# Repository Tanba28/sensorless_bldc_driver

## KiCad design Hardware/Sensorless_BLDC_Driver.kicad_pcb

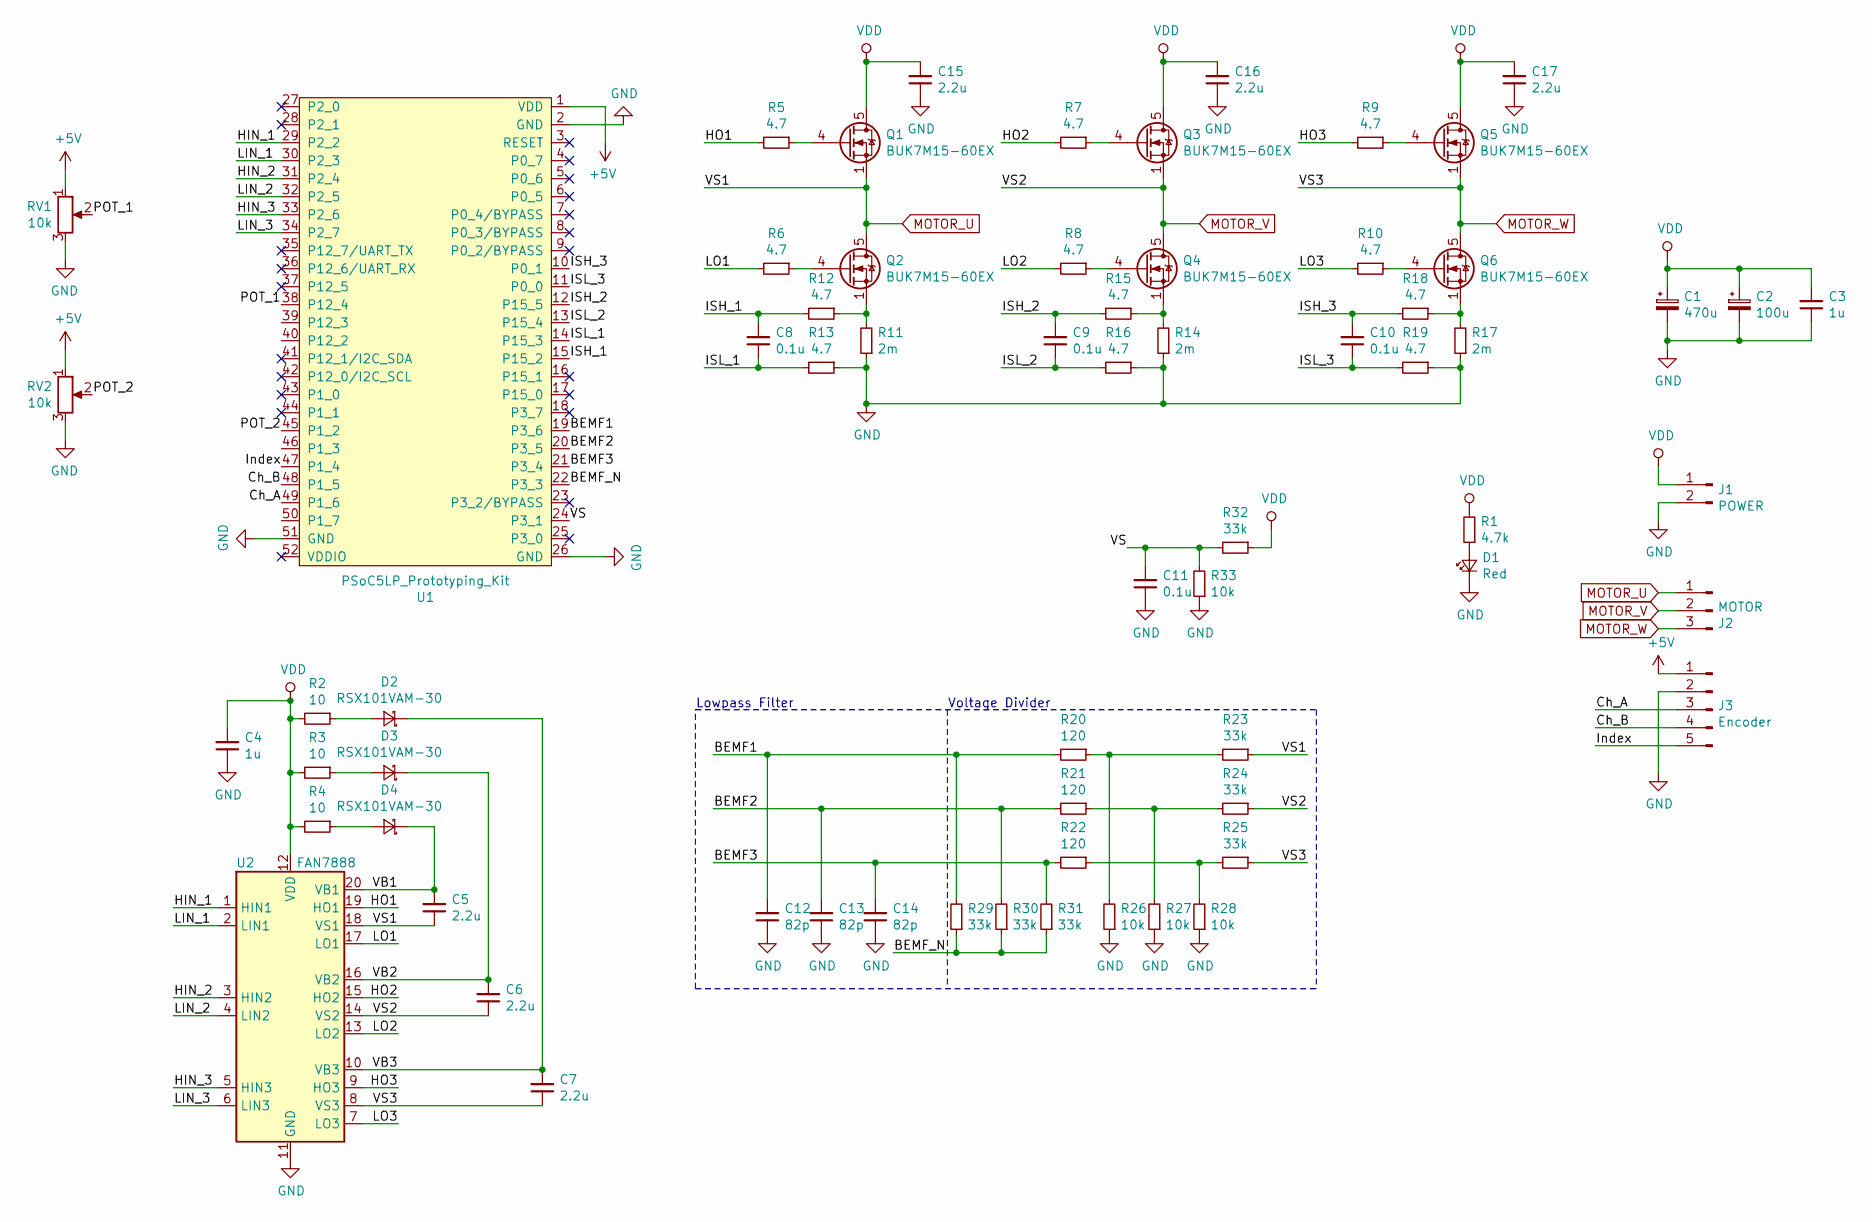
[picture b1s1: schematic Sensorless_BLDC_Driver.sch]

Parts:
C1: 470u; CP_Elec_10x10
C2: 100u; CP_Elec_6.3x7.7; MPN UWT1E471MNL1GS
C3, C4: 1u; C_0402_1005Metric; MPN GRM155R61E105KA12D
C5, C6, C7, C15, C16, C17: 2.2u; C_0603_1608Metric; MPN GRM188R61E225MA12D
C8, C9, C10, C11: 0.1u; C_0402_1005Metric; MPN GRM155R62A104KE14D
C12, C13, C14: 82p; C_0402_1005Metric; MPN GRM1555C1H820JA01D
D1: Red; LED_0603_1608Metric
D2, D3, D4: RSX101VAM-30; D_TUMD2; MPN RSX101VAM-30TR
J1: POWER; Hirose_DF22_DF22x-2P-7.92DSA_1x02_P7.92mm_Vertical; MPN DF22-3P-7.92DSA
J2: MOTOR; Hirose_DF22_DF22x-3P-7.92DSA_1x03_P7.92mm_Vertical; MPN DF22-3P-7.92DSA
J3: Encoder; Hirose_DF1E_DF1E-5P-2.5DS_1x05_P2.5mm_Vertical
Q1, Q2, Q3, Q4, Q5, Q6: BUK7M15-60EX; LFPAK33; MPN BUK7M15-60EX
R1: 4.7k; R_0402_1005Metric; MPN ERJ-2GEJ472X
R2, R3, R4: 10; R_0402_1005Metric; MPN ERJ-2RKF10R0X
R5, R6, R7, R8, R9, R10, R12, R13, R15, R16, R18, R19: 4.7; R_0402_1005Metric; MPN ERJ-2GEJ4R7X
R11, R14, R17: 2m; R_0805_2012Metric; MPN PMR10EZPFV2L00
R20, R21, R22: 120; R_0402_1005Metric; MPN ERJ-2RKF1200X
R23, R24, R25, R29, R30, R31, R32: 33k; R_0402_1005Metric; MPN ERJ-2RKF3302X
R26, R27, R28, R33: 10k; R_0402_1005Metric; MPN ERJ-2GEJ103X
RV1, RV2: 10k; Potentiometer_Alps_RK09K_Single_Vertical
U1: PSoC5LP_Prototyping_Kit; CY8CKIT-059
U2: FAN7888; SOIC-20W_7.5x12.8mm_P1.27mm; MPN FAN7888MX

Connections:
+5V: J3.1, RV1.1, RV2.1, U1.1 (VDD)
/BEMF1: C12.2, R20.2, R29.2, U1.19 (P3_6)
/BEMF2: C13.2, R21.2, R30.2, U1.20 (P3_5)
/BEMF3: C14.2, R22.2, R31.2, U1.21 (P3_4)
/BEMF_N: R29.1, R30.1, R31.1, U1.22 (P3_3)
/Ch_A: J3.3, U1.49 (P1_6)
/Ch_B: J3.4, U1.48 (P1_5)
/HIN_1: U1.29 (P2_2), U2.1 (HIN1)
/HIN_2: U1.31 (P2_4), U2.3 (HIN2)
/HIN_3: U1.33 (P2_6), U2.5 (HIN3)
/HO1: R5.2, U2.19 (HO1)
/HO2: R7.2, U2.15 (HO2)
/HO3: R9.2, U2.9 (HO3)
/ISH_1: C8.2, R12.2, U1.15 (P15_2)
/ISH_2: C9.2, R15.2, U1.12 (P15_5)
/ISH_3: C10.2, R18.2, U1.10 (P0_1)
/ISL_1: C8.1, R13.2, U1.14 (P15_3)
/ISL_2: C9.1, R16.2, U1.13 (P15_4)
/ISL_3: C10.1, R19.2, U1.11 (P0_0)
/Index: J3.5, U1.47 (P1_4)
/LIN_1: U1.30 (P2_3), U2.2 (LIN1)
/LIN_2: U1.32 (P2_5), U2.4 (LIN2)
/LIN_3: U1.34 (P2_7), U2.6 (LIN3)
/LO1: R6.2, U2.17 (LO1)
/LO2: R8.2, U2.13 (LO2)
/LO3: R10.2, U2.7 (LO3)
/POT_1: RV1.2, U1.38 (P12_4)
/POT_2: RV2.2, U1.45 (P1_2)
/VB1: C5.2, D4.1 (K), U2.20 (VB1)
/VB2: C6.2, D3.1 (K), U2.16 (VB2)
/VB3: C7.2, D2.1 (K), U2.10 (VB3)
/VS: C11.2, R32.2, R33.2, U1.24 (P3_1)
GND: C1.2, C2.2, C3.1, C4.1, C11.1, C12.1, C13.1, C14.1, C15.1, C16.1, C17.1, D1.1 (K), J1.2, J3.2, R11.1, R13.1, R14.1, R16.1, R17.1, R19.1, R26.1, R27.1, R28.1, R33.1, RV1.3, RV2.3, U1.2 (GND), U1.26 (GND), U1.51 (GND), U2.11 (GND)
MOTOR_U: C5.1, J2.1, Q1.1 (S), Q1.2 (S), Q1.3 (S), Q2.5 (D), R23.1, U2.18 (VS1)
MOTOR_V: C6.1, J2.2, Q3.1 (S), Q3.2 (S), Q3.3 (S), Q4.5 (D), R24.1, U2.14 (VS2)
MOTOR_W: C7.1, J2.3, Q5.1 (S), Q5.2 (S), Q5.3 (S), Q6.5 (D), R25.1, U2.8 (VS3)
unnamed: D1.2 (A), R1.1
unnamed: D2.2 (A), R2.1
unnamed: D3.2 (A), R3.1
unnamed: D4.2 (A), R4.1
unnamed: Q1.4 (G), R5.1
unnamed: Q2.1 (S), Q2.2 (S), Q2.3 (S), R11.2, R12.1
unnamed: Q2.4 (G), R6.1
unnamed: Q3.4 (G), R7.1
unnamed: Q4.1 (S), Q4.2 (S), Q4.3 (S), R14.2, R15.1
unnamed: Q4.4 (G), R8.1
unnamed: Q5.4 (G), R9.1
unnamed: Q6.1 (S), Q6.2 (S), Q6.3 (S), R17.2, R18.1
unnamed: Q6.4 (G), R10.1
unnamed: R20.1, R23.2, R26.2
unnamed: R21.1, R24.2, R27.2
unnamed: R22.1, R25.2, R28.2
VDD: C1.1, C2.1, C3.2, C4.2, C15.2, C16.2, C17.2, J1.1, Q1.5 (D), Q3.5 (D), Q5.5 (D), R1.2, R2.2, R3.2, R4.2, R32.1, U2.12 (VDD)

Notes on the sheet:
Lowpass Filter
Voltage Divider

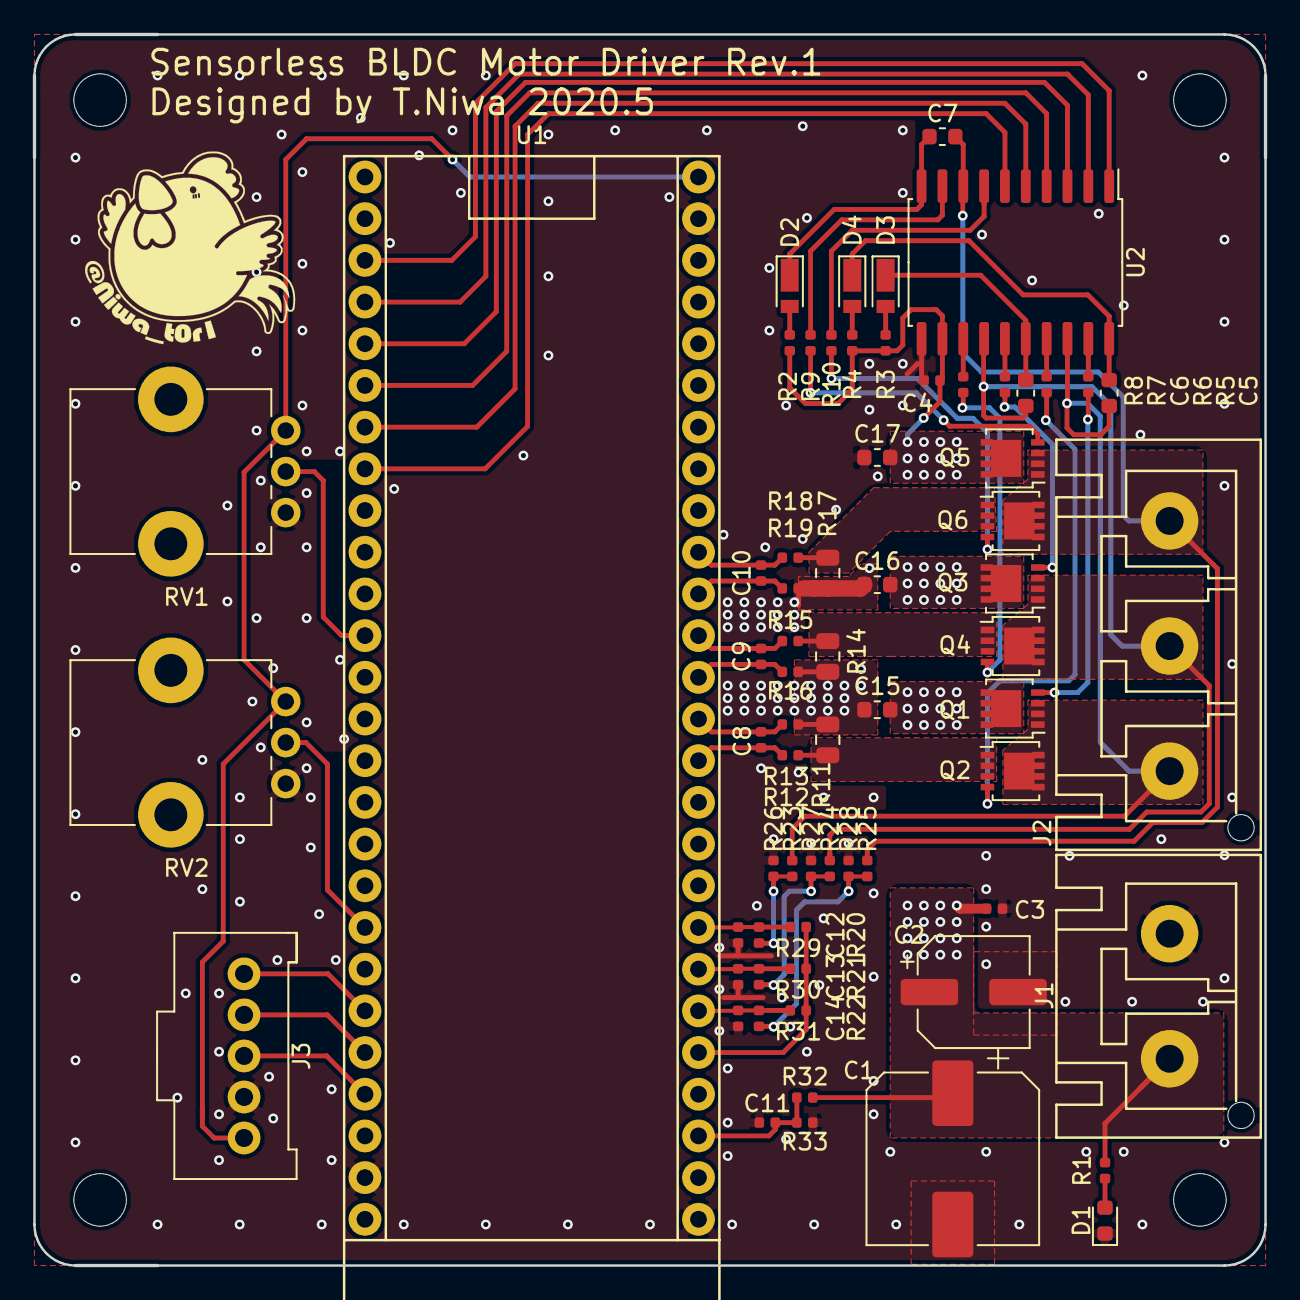
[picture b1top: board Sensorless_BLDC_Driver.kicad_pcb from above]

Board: 2 copper layers, 75.0 x 75.0 mm, 67 parts (0 on the bottom side), 53 nets.

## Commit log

2020-04-28 [add] add KiCAD project file
2020-04-28 [add] add 3-phased half bridge to the schematic
2020-04-28 [add] add u-controller
2020-04-29 [add] add 3-phased current sense
2020-04-29 [update] anotated
2020-05-01 [add] Current Sense
2020-05-01 [add] PSoC Creator Project
2020-05-02 [update] update .gitignore
2020-05-02 [add] assign footprint
2020-05-02 [add] add VDD pass capacitor
2020-05-02 [add] add VDD feedback
2020-05-02 [add] add PCB file and conplete power line
2020-05-03 [update] change power connector from DF63 to DF22
2020-05-03 [add] add Encoder
2020-05-03 PCB chotto susunda
2020-05-06 [update] delete allover current sense
2020-05-06 [update] PCB pattern complete
2020-05-06 [update] change pin assign
2020-05-06 [update] adjust silk
2020-05-06 [update] adjust pin assign
2020-05-07 [update] add via
2020-05-08 [add] add Gerber file
